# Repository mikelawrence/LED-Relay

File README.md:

# LED Relay Replacement PCB
This board was designed to act as a relay for multi-color strip LED lighting on my wife's Harley Tri Glide. The Infineon BTS7008 Dual High-Side Switch provides up to 7.5A per channel. The software allows a quick on-off-on sequence that keeps the LEDs lit after the trike is turned off for a programmable delay time in minutes. In addition to the Stay ON sequence the board also allows programming the amount of time to delay time. Set main.c for instructions on how to issue Stay ON sequence.

There are 4 inputs to the LED Relay board:
* +12V - This should be connected through a fuse to the battery and should remain hot even when the trike is off. All power to the outputs comes from this wire.
* ACC1 - This is +12V when the bike is turned on (ignition).
* ACC2 - This is +12V when the LED lights should be on.
* GND - Chassis and negative terminal of the battery.
The current software turns both outputs on when both ACC1 and ACC2 are at +12V but this can easily be changed to two independent outputs each controlled by its own ACC input. When either ACC1 off the micro-controller enters a low power state waiting for ACC1 to go back to +12V. Note with my current setup ACC2 can never go to +12V without ACC1 also going to +12V.

## Status and Testing
* Rev 2.2 PCB has not been ordered or tested. Since there is only one simple change and my Rev 2.1 was modified to Rev 2.2 I feel confident Rev 2.2 is ready for use.
  * Added ACC1 connection to PD2 on micro-controller. Only PIN2 has full asynchronous edge detection needed for ACC1.
  * You can order parts from Mouser using this [shared BOM](http://www.mouser.com/ProjectManager/ProjectDetail.aspx?AccessID=7477630473). Note LT3014 is not available at Mouser you must get it somewhere else like Digikey.
  * You can order the PCB from OSH Park using this [link](https://oshpark.com/shared_projects/Q2hSPIYz) to OSH Park.
* Rev 2.1 PCB has been ordered from OSH Park, assembled, and tested.
  * Added R12 and R13.
  * Moved ACC connections on micro-controller.
  * Testing complete after modifying to Rev 2.2.
* Rev 2.0 PCB.
  * Converted older design to KiCad.
  * Switched from low-side switch to dual high-side switch.
* Rev 1.0 Existed as another design that was close.

## Board Preview

## Notes
* The current usage is only one channel with a typical 4A LED load and maximum of 6A. I have not done any load testing to see how well the board operates with both channels going full bore. The High-Side Switch will shutdown to protect itself if it get too hot.
* When ACC1 is off the XMega8E5 enters an ultra low power mode drawing about 1µA. Add that to the LT3014 linear regulator's quiescent current and this board has standby current of 8µA. In bench testing my first board used 7.8µA at room temperature. Keep in mind this current is likely to double or even triple at higher temperatures but for a motorcycle or car battery this standby current is excellent.
* JP1 must be in place for circuit to work correctly. JP1 is a good scope ground point in testing.
* Assembling the this PCB will require a reflow oven. If you don't have one [Whizoo](http://www.whizoo.com/) sells a nice kit to make your own.
* PCB is designed in [KiCad](http://kicad-pcb.org) which is a great free EDA toolset.

## Software
The microcontroller is a Atmel/Microchip XMega8E5. Software is written in C using the free [Atmel Studio 7](https://www.google.com/search?q=atmel+studio+7). I recommend the Atmel ICE to both debug and program the XMega. Especially since it already has a 50mil PDI connector to plug directly onto the LED Relay board.

## Protection Against the Elements
When mounting on a motorcycle protection against the elements is crucial to longevity so the LED Relay board is thin enough to get 1" adhesive heat shrink on it. Once shrunk the board is well protected and the wires also get some strain relief.

Note I used several different sizes of adhesive heat shrink to get a watertight seal around the wires.

## Final Result
Here is the obligatory end result picture!

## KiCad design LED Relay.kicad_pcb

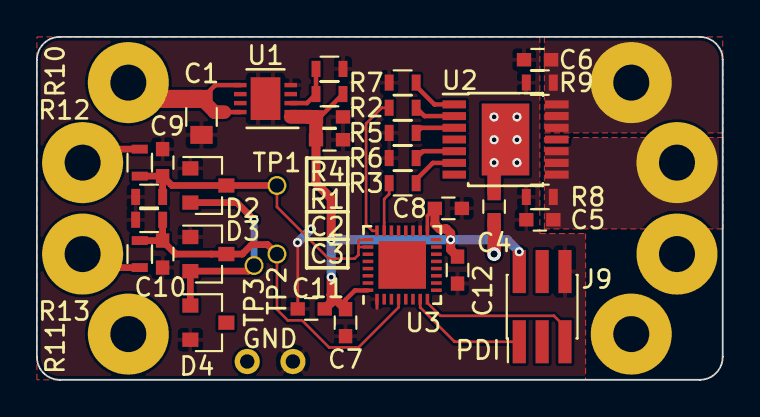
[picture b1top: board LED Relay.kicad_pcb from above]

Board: 2 copper layers, 38.1 x 19.1 mm, 45 parts (1 on the bottom side), 21 nets.

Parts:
C1: 1uF; C_0805
C2, C3, C7, C8: 0.47uF; C_0603
C4: 68nF; C_0603
C5, C6, C9, C10, C11, C12: 10nF; C_0603
D1: SM15T33CA; D_SMC_Handsoldering
D2, D3: BAT54S; SOT-23
D4: ZRC330; SOT-23
J1, J2, J3, J4, J5, J6, J7, J8: TEST_1P; SolderWirePad_single_2mmDrill
J9: Header; Pin_Header_Straight_2x03_Pitch1.27mm_SMD
JP1: GND; WireConnection_0.80mmDrill_ThinPad
R1: 2.15M; R_0603
R2, R3: 4.7k; R_0603
R4: 1.27M; R_0603
R5, R6: 10k; R_0603
R7: 47; R_0603
R8, R9, R10, R11, R12, R13: 47k; R_0603
TP1, TP2, TP3: TEST_1P; SolderWirePad_single_0-8mmDrill
U1: LT3014IDD; DFN-8-1EP_3x3mm_Pitch0.5mm
U2: BTS7008-2EPA; Infineon_PG-TSDSO-14-22
U3: ATXMEGA8E5-M4U; QFN-32-1EP_4x4mm_Pitch0.4mm

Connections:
+3V3: C2.1, C3.1, C7.2, C8.1, C11.1, C12.1, J9.2, R1.2, U1.1, U3.17, U3.32
/+12V: C1.1, C4.2, D1.1, J1.1, U1.5, U1.8, U2.15
/ACC1: J2.1, R10.2
/ACC2: J7.1, R11.2
/PDI_CLK: J9.5, U3.8
/PDI_DATA: J9.1, U3.7
/VOUT1+: C6.1, J3.1, R9.2, U2.12, U2.13, U2.14
/VOUT2+: C5.1, J5.1, R8.2, U2.8, U2.9, U2.10
ACC1_IN: C9.1, D2.3, R10.1, R12.2, TP1.1, U3.25, U3.26
GND: C4.1, D1.2, J4.1, J6.1, J8.1, JP1.1
GNDD: C1.2, C2.2, C3.2, C5.2, C6.2, C7.1, C8.2, C9.2, C10.2, C11.2, C12.2, D2.1, D3.1, D4.2, J9.6, JP1.2, R4.1, R5.1, R6.1, R7.1, R8.1, R9.1, R12.1, R13.1, U1.4, U1.9, U3.1, U3.18
unnamed: C10.1, D3.3, R11.1, R13.2, TP2.1, U3.4
unnamed: D2.2, D3.2, D4.1, TP3.1
unnamed: R1.1, R4.2, U1.2
unnamed: R2.1, U2.2
unnamed: R3.1, U2.6
unnamed: R5.2, U2.3
unnamed: R6.2, U2.5
unnamed: R7.2, U2.1
V1EN: R2.2, U3.24
V2EN: R3.2, U3.23

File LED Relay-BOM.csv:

Qty,Reference, Value,Package, Part Number, Manufacturer, Vendor, Vendor Part Number
6,"C5-C6, C9-C10, C11-C12",10nF,603,GCM188R72A103KA7D,Murata Electronics,Mouser,81-GCM188R72A103KA7D
1,C4,68nF,603,GCJ188R92A683KA01D,Murata Electronics,Mouser,81-GCJ188R92A683KA1D
4,"C2-C3, C7-C8",0.47uF,603,GRM188R71C474KA88,Murata Electronics,Mouser,81-GRM188R71C474KA88
1,C1,1uF,805,GRJ21BC72A105KE11L,Murata Electronics,Mouser,81-GRJ21BC72A105KE1L
1,R7,47,603,RC0603FR-0747RL,Yageo,Mouser,603-RC0603FR-0747RL
2,R2-R3,4.7k,603,RC0603JR-074K7L,Yageo,Mouser,603-RC0603JR-074K7L
2,R5-R6,10k,603,RC0603JR-0710KL,Yageo,Mouser,603-RC0603JR-0710KL
6,"R8-R9, R10-R13",47k,603,603-RC0603JR-0747KL,Yageo,Mouser,603-RC0603JR-0747KL
1,R4,1.27M,603,CRCW06031M27FKEA,Vishay,Mouser,71-CRCW06031M27FKEA
1,R1,2.15M,603,CRCW06032M15FKEA,Vishay,Mouser,71-CRCW06032M15FKEA
2,D2-D3,BAT54S,SOT-23,BAT54S,Nexperia,Mouser,771-BAT54S-T/R
1,D1,SM15T33CA,SMC,SM15T33CA,ST,Mouser,511-SM15T33CA
1,D4,ZRC330,SOT-23,ZRC330F01TA,Diodes Inc.,Mouser,522-ZRC330F01TA
1,U3,ATXMEGA8E5-M4U,QFN-32-1EP,ATXMEGA8E5-M4U,Atmel,Mouser,556-ATXMEGA8E5-M4U
1,U2,BTS7008-2EPA,PG-TSDSO-14-22,BTS70082EPAXUMA1,Infineon,Mouser,726-BTS70082EPAXUMA1
1,U1,LT3014IDD,DFN-8-1EP,LT3014BHVIDD#PBF,Linear Tech,Digikey,LT3014BHVIDD#PBF-ND
1,J9,Header,6-Pin Header,20021121-00006C4LF,Amphenol/FCi,Mouser,649-202112100006C4LF

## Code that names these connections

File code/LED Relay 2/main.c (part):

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#define V12EN_port						PORTD
#define V1EN_bp							PIN4_bp
#define V2EN_bp							PIN5_bp
#define ACC1_port						PORTD
#define ACC1_bp							PIN2_bp
#define ACC2_port						PORTA
#define ACC2_bp							PIN2_bp
/*
 * Inferred definitions
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#define V2EN_OFF()						V12EN_port.OUTCLR = _BV(V2EN_bp)
#define V12EN_ON()						V12EN_port.OUTSET = (_BV(V1EN_bp) | _BV(V2EN_bp))
#define V12EN_OFF()						V12EN_port.OUTCLR = (_BV(V1EN_bp) | _BV(V2EN_bp))
#define IS_ACC1_ON()					(ACC1_port.IN & _BV(ACC1_bp))
#define IS_ACC2_ON()					(ACC2_port.IN & _BV(ACC2_bp))
#define MAIN_TCNT_FROM_SECONDS(sec)		(uint16_t) round(sec / 0.001)


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
volatile uint8_t  acc1_debounce = 0;
volatile uint8_t  acc1_last;						// Last ACC1 state
volatile uint16_t acc1_on_start_time = 0;			// The value of Main Timer Count when ACC1 ON started
volatile uint16_t acc1_off_start_time = 0;			// The value of Main Timer Count when ACC1 OFF started

volatile uint8_t  acc2_debounce = 0;
volatile uint8_t  acc2_last;						// Last ACC2 state
volatile uint16_t acc2_on_start_time = 0;			// The value of Main Timer Count when ACC2 ON started
volatile uint16_t acc2_off_start_time = 0;			// The value of Main Timer Count when ACC2 OFF started

int main(void)
{
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	uint8_t  stayon_state = SM_STAYON_RESET;		// Current sequence state
	uint8_t  prog_state = SM_PROG_RESET;			// Current programming state
	uint8_t  wait_minutes;							// Number of minutes to stay on
	uint16_t acc1_on_time = 0;						// ACC1 length of time on
	uint16_t acc1_off_time = 0;						// ACC1 length of time off
	uint16_t acc2_on_time = 0;						// ACC2 length of time on
	uint16_t acc2_off_time = 0;						// ACC2 length of time off
	uint16_t tick_cnt_ms;							// Current time in ms (max 65.535 seconds)
	uint8_t  flash_count = 0;						// The number of valid program flashes received on ACC2
	
	// Disable the Watchdog timer on start
	wdt_disable();
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			PORTR.PIN0CTRL = PORT_OPC_PULLDOWN_gc | PORT_ISC_BOTHEDGES_gc;	// PORTR is all pullups
			// Configure ACC1
			PORTCFG.MPCMASK = _BV(ACC1_bp) | _BV(3);
			ACC1_port.PIN0CTRL = PORT_OPC_TOTEM_gc | PORT_ISC_BOTHEDGES_gc;	// Input NO pullup and interrupt on any edge
			ACC1_port.INTCTRL = PORT_INTLVL_HI_gc;							// Interrupt will be high level
			ACC1_port.INTMASK |= _BV(ACC1_bp);								// Port interrupt enabled
			// Configure ACC2
			PORTCFG.MPCMASK = _BV(ACC2_bp);
			ACC2_port.PIN0CTRL = PORT_OPC_TOTEM_gc | PORT_ISC_BOTHEDGES_gc;	// Input NO pullup and interrupt on any edge
			ACC2_port.INTCTRL = PORT_INTLVL_HI_gc;							// Interrupt will be high level
			ACC2_port.INTMASK |= _BV(ACC2_bp);								// Port interrupt enabled
			// Configure V1EN and V2EN as totem-pole outputs
			V12EN_port.OUTCLR = _BV(V1EN_bp) | _BV(V2EN_bp);				// V1EN and V2EN will be low when enabled
			PORTCFG.MPCMASK = _BV(V1EN_bp) | _BV(V2EN_bp);
			V12EN_port.PIN0CTRL = PORT_OPC_TOTEM_gc;						// V1EN and V2EN will be totem-pole outputs
			V12EN_port.DIRSET = _BV(V1EN_bp) | _BV(V2EN_bp);				// V1EN and V2EN are now outputs
			// Configure Power Reduction
			PR.PRGEN = 1 << PR_XCL_bp				// XCL power down: enabled
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
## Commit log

2017-08-19 Upped Rev to 2.1. Added R12 and R13. Moved connections on micro-controller.
2017-08-19 Added Rev 2.1 summary to README.
2017-08-19 Upped Rev to 2.2. Added ACC1 connect to PD2 on micro-controller.
2017-08-19 First code commit.
2017-08-19 Updated README for Rev 2.2.
2017-08-19 Added final picture.
2017-08-20 Add README images. Added comment to main.c.
2017-08-20 Removed accidentally included backup file.
2017-08-20 Cleanup
    Updated Status in README file. Removed *.bak files.
